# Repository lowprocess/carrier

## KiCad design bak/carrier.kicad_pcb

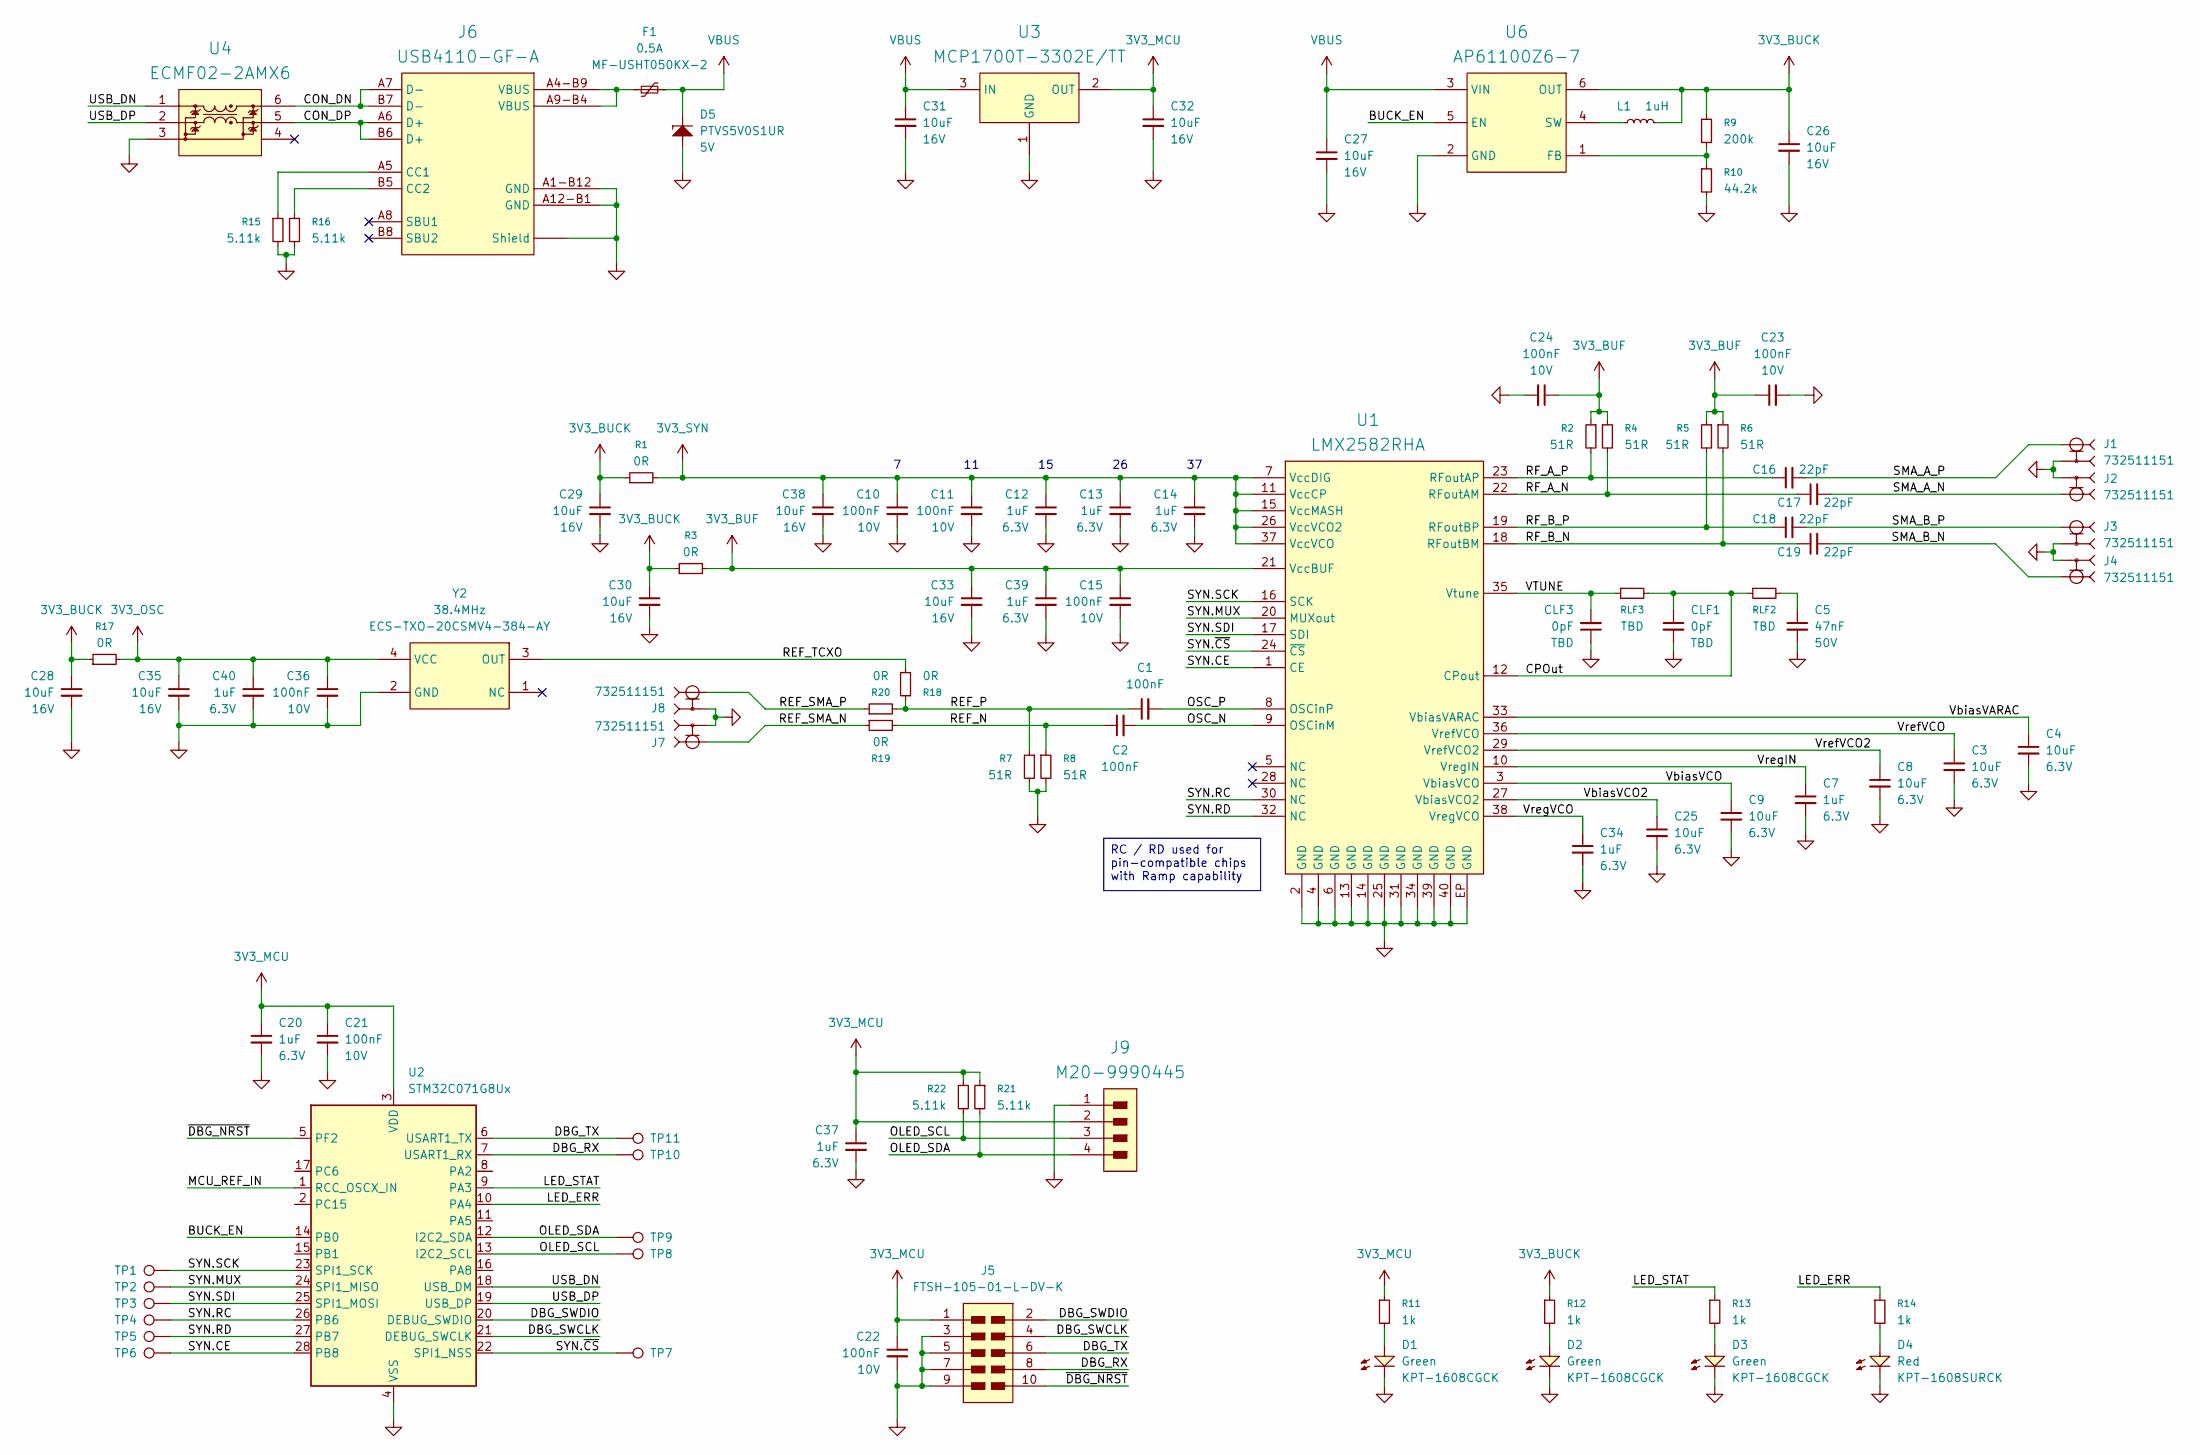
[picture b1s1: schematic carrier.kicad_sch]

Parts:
C1, C2, C10, C11, C15, C21, C22, C23, C24, C36: 100nF; C_0402; Tolerance 10%; Voltage 10V; PartNumber GRM155R71A104K
C3, C4, C8, C9, C25: 10uF; C_0402; Tolerance 20%; Voltage 6.3V; PartNumber GRM155R60J106M
C5: 47nF; C_1206; Tolerance 5%; Voltage 50V; PartNumber C1206C473J5GACTU
C7, C12, C13, C14, C20, C34, C37, C39, C40: 1uF; C_0402; Tolerance 10%; Voltage 6.3V; PartNumber GRM155R70J105K
C16, C17, C18, C19: 22pF; C_0201; Tolerance 5%; Voltage 25V; PartNumber GRM0335C1E220J
C26, C27, C28, C29, C30, C31, C32, C33, C35, C38: 10uF; C_0805; Tolerance 10%; Voltage 16V; PartNumber GRM21BR61C106K
CLF1, CLF3: 0pF; C_0402; Tolerance TBD; Voltage TBD; PartNumber 0402_TBD
D1, D2, D3: Green; LED_0603; PartNumber KPT-1608CGCK
D4: Red; LED_0603; PartNumber KPT-1608SURCK
D5: SOD123W; PartNumber PTVS5V0S1UR
F1: 0.5A; F_1210; PartNumber MF-USHT050KX-2
J1, J2, J3, J4, J7, J8: 732511151; Molex 73251-1151; PartNumber 732511151
J5: FTSH-105-01-L-DV-K; FTSH-105-01-X-DV-K; PartNumber FTSH-105-01-L-DV-K
J6: USB4110-GF-A; USB-C USB4110; PartNumber USB4110-GF-A
J9: M20-9990445; Header 2.54 1x04 Staggered; PartNumber M20-9990445
L1: 1uH; L_252010; Tolerance 20%; PartNumber CIGT252010EH1R0MNE
R1, R3, R17, R18, R19, R20: 0R; R_0402; Tolerance 0%; PartNumber CRCW04020000Z0ED
R2, R4, R5, R6, R7, R8: 51R; R_0201; Tolerance 1%; PartNumber CRCW020151R0FNED
R9: 200k; R_0402; Tolerance 1%; PartNumber RC0402FR-07200KL
R10: 44.2k; R_0402; Tolerance 1%; PartNumber RC0402FR-0744K2L
R11, R12, R13, R14: 1k; R_0402; Tolerance 1%; PartNumber CRCW04021K00FKED
R15, R16, R21, R22: 5.11k; R_0402; Tolerance 1%; PartNumber RC0402FR-075K11L
RLF2, RLF3: TBD; R_0402; Tolerance TBD; PartNumber 0402_TBD
TP1: SCK; Testpad_1mm
TP2: MUX; Testpad_1mm
TP3: SDI; Testpad_1mm
TP4: RC; Testpad_1mm
TP5: RD; Testpad_1mm
TP6: CE; Testpad_1mm
TP7: CS; Testpad_1mm
TP8: SCL; Testpad_1mm
TP9, TP10, TP11: SDA; Testpad_1mm
U1: QFN40; PartNumber LMX2582RHA
U2: STM32C071G8Ux; QFN-28_4x4mm_P0.5mm
U3: SOT-23-3; PartNumber MCP1700T-3302E/TT
U4: DFN6-1.55x1.75; PartNumber ECMF02-2AMX6
U6: SOT563; PartNumber AP61100Z6-7
Y2: 38.4MHz; XTAL2016-4; PartNumber ECS-TXO-20CSMV4-384-AY

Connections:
3V3_BUCK: C26.1, C28.1, C29.1, C30.1, L1.2, R1.1, R3.1, R9.1, R12.1, R17.1, U6.6 (OUT)
3V3_BUF: C15.1, C23.1, C24.1, C33.1, C39.1, R2.1, R3.2, R4.1, R5.1, R6.1, U1.21 (VccBUF)
3V3_MCU: C20.1, C21.1, C22.1, C32.1, C37.1, J5.1, J9.2, R11.1, R21.1, R22.1, U2.3 (VDD), U3.2 (OUT)
3V3_OSC: C35.1, C36.1, C40.1, R17.2, Y2.4 (VCC)
3V3_SYN: C10.1, C11.1, C12.1, C13.1, C14.1, C38.1, R1.2, U1.7 (VccDIG), U1.11 (VccCP), U1.15 (VccMASH), U1.26 (VccVCO2), U1.37 (VccVCO)
/BUCK_EN: U2.14 (PB0), U6.5 (EN)
/CON_DN: J6.A7 (D-), J6.B7 (D-), U4.6 (IC+)
/CON_DP: J6.A6 (D+), J6.B6 (D+), U4.5 (IC-)
/CPOut: CLF1.1, RLF2.1, RLF3.2, U1.12 (CPout)
/DBG_RX: J5.8, TP10.1 (1_1), U2.7 (USART1_RX)
/DBG_SWCLK: J5.4, U2.21 (DEBUG_SWCLK)
/DBG_SWDIO: J5.2, U2.20 (DEBUG_SWDIO)
/DBG_TX: J5.6, TP11.1 (1_1), U2.6 (USART1_TX)
/LED_ERR: R14.1, U2.10 (PA4)
/LED_STAT: R13.1, U2.9 (PA3)
/MCU_REF_IN: U2.1 (RCC_OSCX_IN)
/OLED_SCL: J9.3, R22.2, TP8.1 (1_1), U2.13 (I2C2_SCL)
/OLED_SDA: J9.4, R21.2, TP9.1 (1_1), U2.12 (I2C2_SDA)
/OSC_N: C2.2, U1.9 (OSCinM)
/OSC_P: C1.2, U1.8 (OSCinP)
/REF_N: C2.1, R8.1, R19.2
/REF_P: C1.1, R7.1, R18.2, R20.2
/REF_SMA_N: J7.inner (Inner), R19.1
/REF_SMA_P: J8.inner (Inner), R20.1
/REF_TCXO: R18.1, Y2.3 (OUT)
/RF_A_N: C17.1, R4.2, U1.22 (RFoutAM)
/RF_A_P: C16.1, R2.2, U1.23 (RFoutAP)
/RF_B_N: C19.1, R6.2, U1.18 (RFoutBM)
/RF_B_P: C18.1, R5.2, U1.19 (RFoutBP)
/SMA_A_N: C17.2, J2.inner (Inner)
/SMA_A_P: C16.2, J1.inner (Inner)
/SMA_B_N: C19.2, J4.inner (Inner)
/SMA_B_P: C18.2, J3.inner (Inner)
/SYN.CE: TP6.1 (1_1), U1.1 (CE), U2.28 (PB8)
/SYN.MUX: TP2.1 (1_1), U1.20 (MUXout), U2.24 (SPI1_MISO)
/SYN.RC: TP4.1 (1_1), U1.30 (NC), U2.26 (PB6)
/SYN.RD: TP5.1 (1_1), U1.32 (NC), U2.27 (PB7)
/SYN.SCK: TP1.1 (1_1), U1.16 (SCK), U2.23 (SPI1_SCK)
/SYN.SDI: TP3.1 (1_1), U1.17 (SDI), U2.25 (SPI1_MOSI)
/SYN.~CS: TP7.1 (1_1), U1.24 (~CS), U2.22 (SPI1_NSS)
/USB_DN: U2.18 (USB_DM), U4.1 (CON+)
/USB_DP: U2.19 (USB_DP), U4.2 (CON-)
/VTUNE: CLF3.2, RLF3.1, U1.35 (Vtune)
/VbiasVARAC: C4.1, U1.33 (VbiasVARAC)
/VbiasVCO: C9.1, U1.3 (VbiasVCO)
/VbiasVCO2: C25.1, U1.27 (VbiasVCO2)
/VrefVCO: C3.1, U1.36 (VrefVCO)
/VrefVCO2: C8.1, U1.29 (VrefVCO2)
/VregIN: C7.1, U1.10 (VregIN)
/VregVCO: C34.1, U1.38 (VregVCO)
/~DBG_NRST: J5.10, U2.5 (PF2)
GND: C3.2, C4.2, C5.2, C7.2, C8.2, C9.2, C10.2, C11.2, C12.2, C13.2, C14.2, C15.2, C20.2, C21.2, C22.2, C23.2, C24.2, C25.2, C26.2, C27.2, C28.2, C29.2, C30.2, C31.2, C32.2, C33.2, C34.2, C35.2, C36.2, C37.2, C38.2, C39.2, C40.2, CLF1.2, CLF3.1, D1.K, D2.K, D3.K, D4.K, D5.A, J1.outer (Outer), J2.outer (Outer), J3.outer (Outer), J4.outer (Outer), J5.3, J5.5, J5.7, J5.9, J6.A1-B12 (GND), J6.A12-B1 (GND), J6.SH (Shield), J7.outer (Outer), J8.outer (Outer), J9.1, R7.2, R8.2, R10.2, R15.2, R16.2, U1.2 (GND), U1.4 (GND), U1.6 (GND), U1.13 (GND), U1.14 (GND), U1.25 (GND), U1.31 (GND), U1.34 (GND), U1.39 (GND), U1.40 (GND), U1.EP (GND), U2.4 (VSS), U3.1 (GND), U4.3 (GND), U6.2 (GND), Y2.2 (GND); also elsewhere on the board
unnamed 52: C5.1, RLF2.2; also elsewhere on the board
unnamed: D1.A, R11.2
unnamed: D2.A, R12.2
unnamed: D3.A, R13.2
unnamed: D4.A, R14.2
unnamed: F1.1, J6.A4-B9 (VBUS), J6.A9-B4 (VBUS)
unnamed: J6.A5 (CC1), R15.1
unnamed: J6.B5 (CC2), R16.1
unnamed: R9.2, R10.1, U6.1 (FB)
unnamed: L1.1, U6.4 (SW)
VBUS: C27.1, C31.1, D5.K, F1.2, U3.3 (IN), U6.3 (VIN)

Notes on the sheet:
RC / RD used for pin-compatible chips with Ramp capability

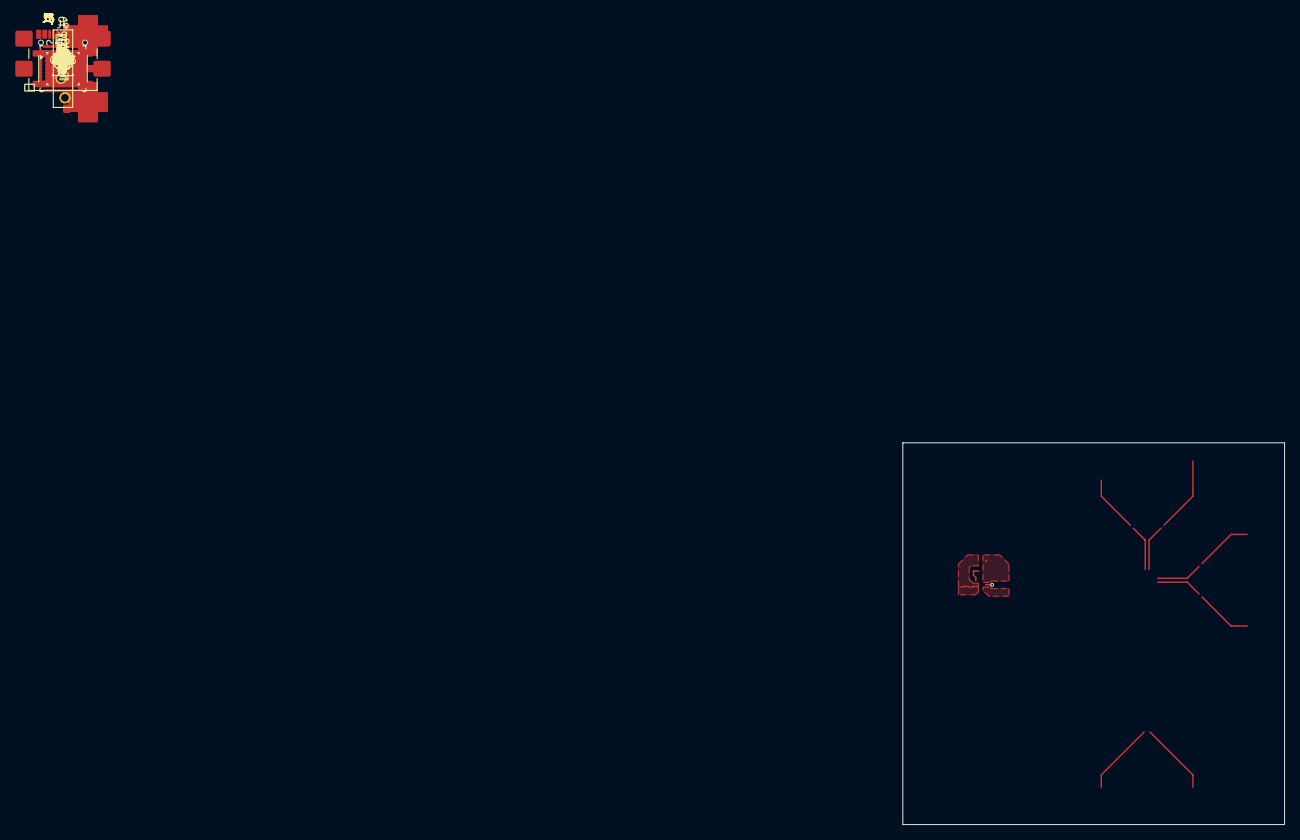
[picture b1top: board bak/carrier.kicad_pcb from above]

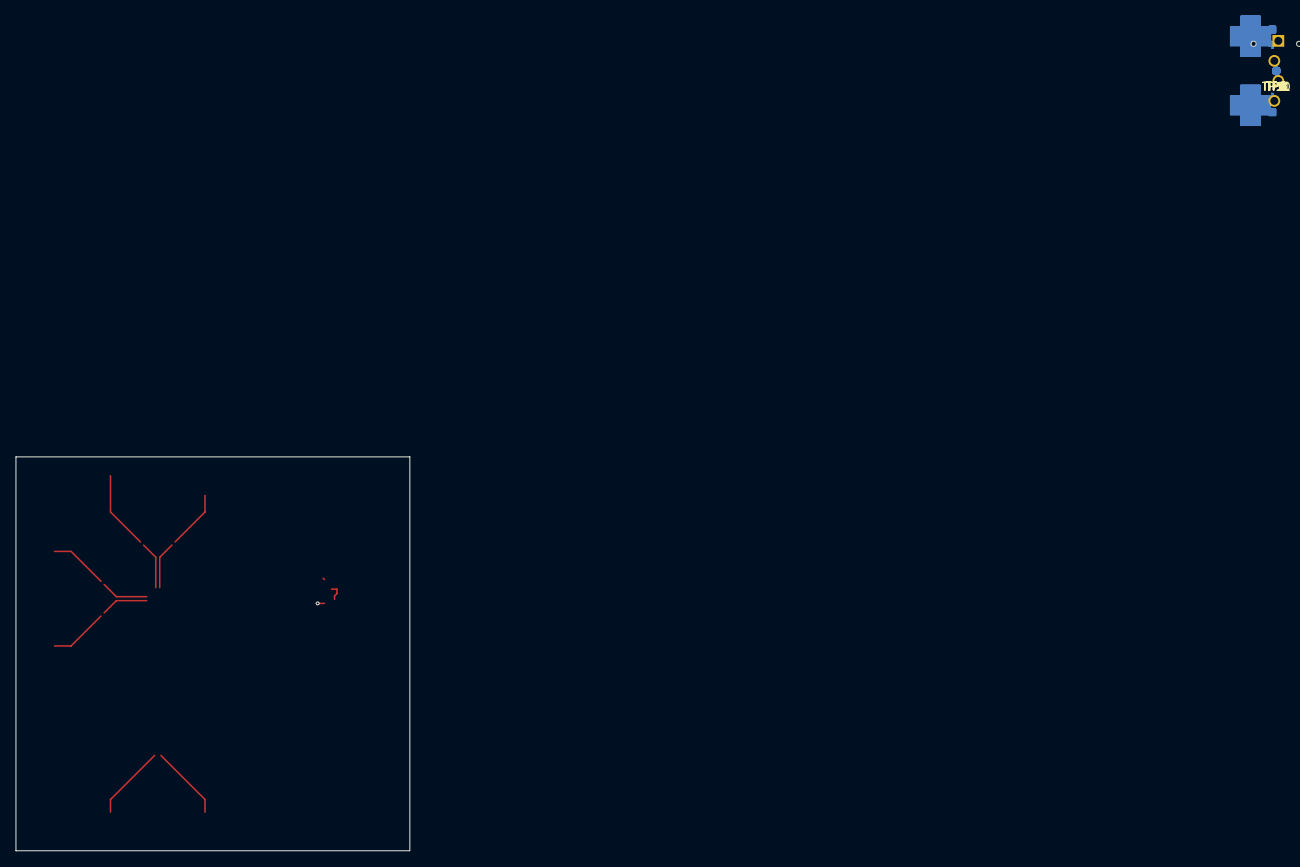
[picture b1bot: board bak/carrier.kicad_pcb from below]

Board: 2 copper layers, 50.0 x 50.0 mm, 98 parts (11 on the bottom side), 62 nets.

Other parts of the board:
CLF2: 0pF; C_0402

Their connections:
GND: CLF2.2; also elsewhere on the board
unnamed 52: CLF2.1; also elsewhere on the board

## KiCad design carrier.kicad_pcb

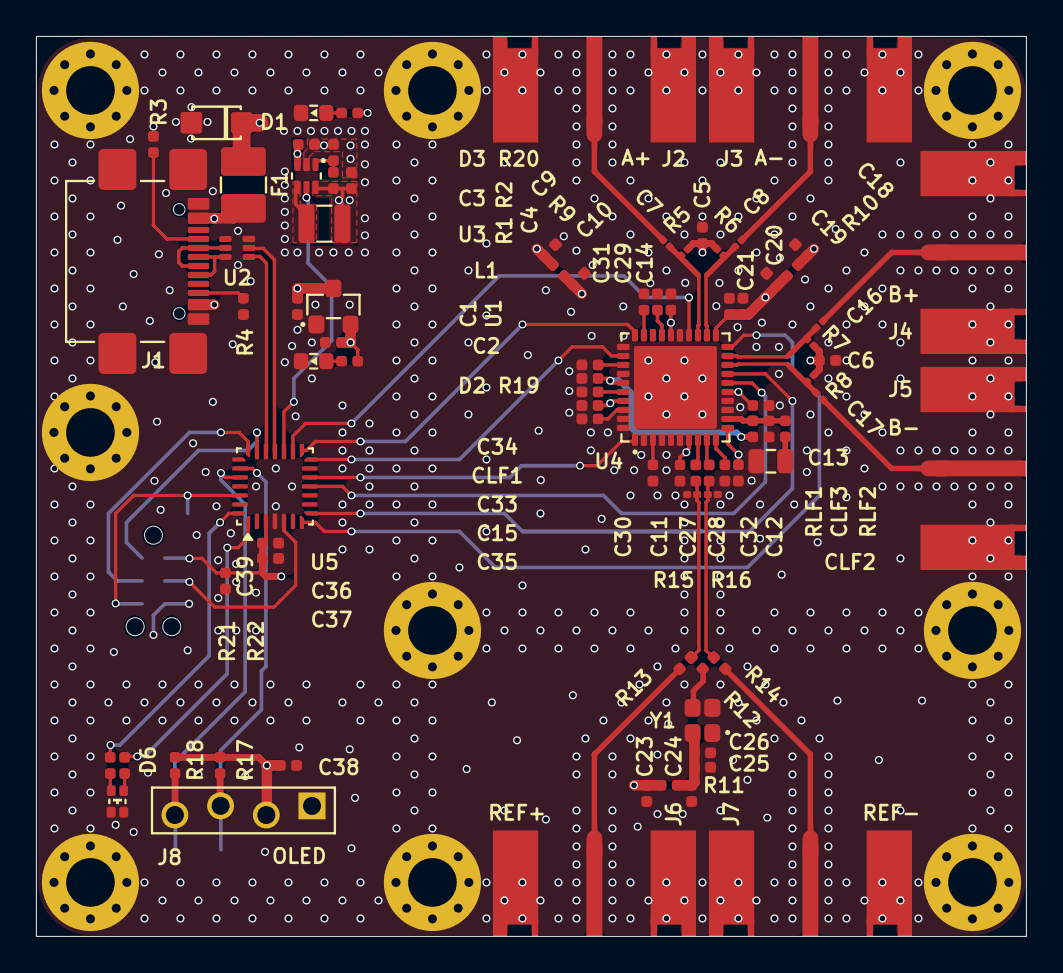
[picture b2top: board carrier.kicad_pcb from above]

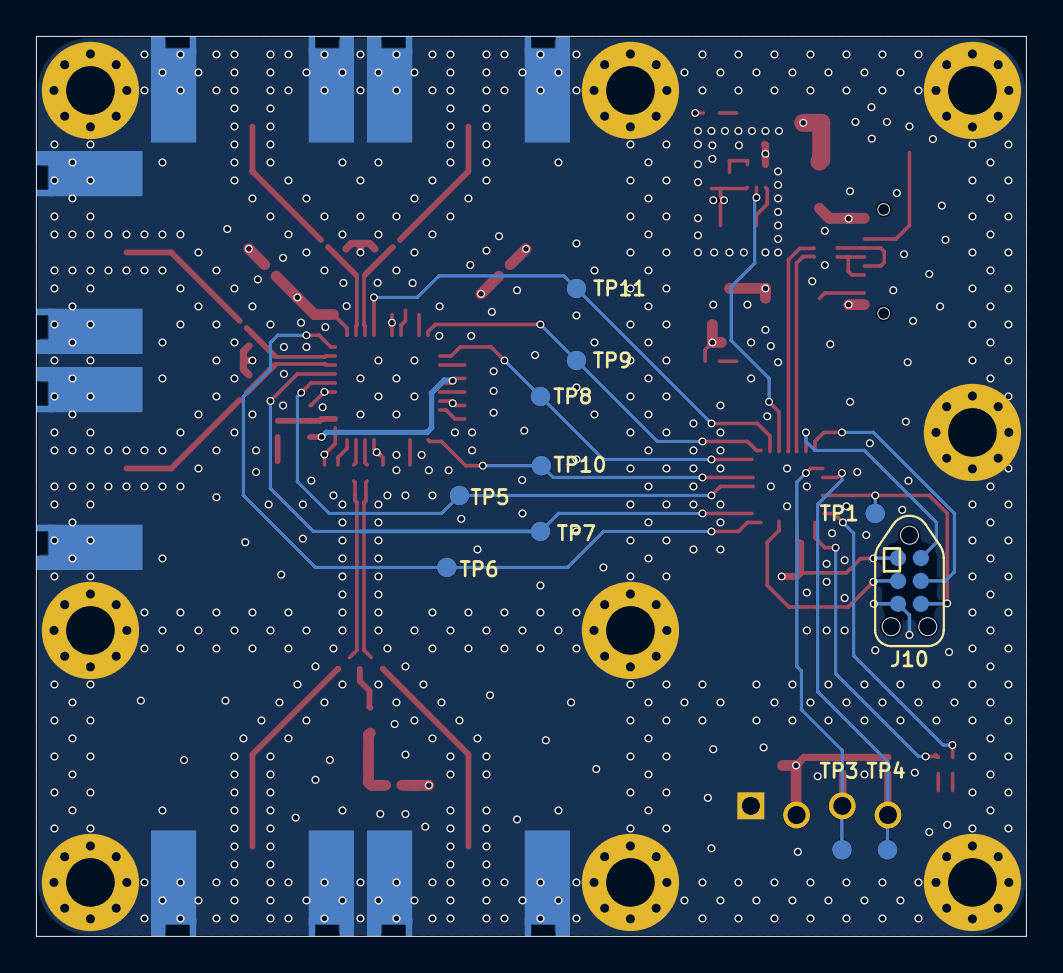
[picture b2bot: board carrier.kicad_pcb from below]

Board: 4 copper layers, 55.0 x 50.0 mm, 105 parts (11 on the bottom side), 61 nets.

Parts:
C1, C2, C3, C4, C9, C10, C18, C19, C23, C24, C29, C30, C31, C33, C34: 10uF; C_0402
C5, C6, C11, C12, C21, C26, C27, C28, C37, C39: 100nF; C_0402
C7, C8, C16, C17: 22pF; C_0201
C13, C14, C15, C20, C25, C32, C35, C36, C38: 1uF; C_0402
CLF1, CLF3: 0pF; C_0402
CLF2: 10nF; C_0805
D1: SOD123W
D2, D3: Green; LED_0603
D6: RG; APHB1608GR
F1: 0.5A; F_1210
H1, H2, H3, H4, H5, H6, H7, H8, H9: GND; MountingHole_2.7mm_M2.5_Pad_Via
J1: USB4110-GF-A; USB-C USB4110
J2, J3, J4, J5, J6, J7: 732511151; Molex 73251-1151
J8: M20-9990445; Header 2.54 1x04 Staggered
J10: TC2030-NL-FP; TC2030-xxx-NL
L1: 1uH; L_252010
R1: 200k; R_0402
R2: 44.2k; R_0402
R3, R4, R17, R18: 5.11k; R_0402
R5, R6, R7, R8, R15, R16: 51R; R_0201
R9, R10, R11, R12, R13, R14: 0R; R_0402
R19, R20, R21, R22: 1k; R_0402
RLF1, RLF2: TBD; R_0402
TP1, TP3: SDA; Testpad_1mm
TP4: SCL; Testpad_1mm
TP5: SCK; Testpad_1mm
TP6: MUX; Testpad_1mm
TP7: SDI; Testpad_1mm
TP8: RC; Testpad_1mm
TP9: RD; Testpad_1mm
TP10: CE; Testpad_1mm
TP11: CS; Testpad_1mm
U1: SOT-23-3
U2: DFN6-1.55x1.75
U3: SOT563
U4: QFN40
U5: STM32C071G8Ux; QFN-28_4x4mm_P0.5mm
Y1: 38.4MHz; XTAL2016-4

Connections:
3V3_BUCK: C4.1, C9.1, C18.1, L1.2, R1.1, R9.1, R10.1, R20.1, U3.6 (OUT)
3V3_BUF: C5.1, C6.1, C19.1, C20.1, C21.1, R5.1, R6.1, R7.1, R8.1, R10.2, U4.21 (VccBUF)
3V3_MCU: C2.1, C23.1, C36.1, C37.1, C38.1, C39.1, J8.2, J10.1, R11.1, R17.1, R18.1, R19.1, U1.2 (OUT), U5.3 (VDD)
3V3_OSC: C24.1, C25.1, C26.1, R11.2, Y1.4 (VCC)
3V3_SYN: C10.1, C11.1, C12.1, C13.1, C14.1, C15.1, R9.2, U4.7 (VccDIG), U4.11 (VccCP), U4.15 (VccMASH), U4.26 (VccVCO2), U4.37 (VccVCO)
/BUCK_EN: U3.5 (EN), U5.17 (PC6)
/CON_DN: J1.A7 (D-), J1.B7 (D-), U2.5 (IC-)
/CON_DP: J1.A6 (D+), J1.B6 (D+), U2.6 (IC+)
/CPOut: CLF3.1, RLF1.2, RLF2.1, U4.12 (CPout)
/DBG_SWCLK: J10.4, U5.21 (DEBUG_SWCLK)
/DBG_SWDIO: J10.2, U5.20 (DEBUG_SWDIO)
/DBG_TX: J10.6, TP1.1 (1_1), U5.26 (USART1_TX)
/LED_ERR: R22.1, U5.1 (PC14)
/LED_STAT: R21.1, U5.28 (PB8)
/OLED_SCL: J8.3, R17.2, TP3.1 (1_1), U5.23 (I2C2_SCL)
/OLED_SDA: J8.4, R18.2, TP4.1 (1_1), U5.24 (I2C2_SDA)
/OSC_N: C28.2, U4.9 (OSCinM)
/OSC_P: C27.2, U4.8 (OSCinP)
/REF_N: C28.1, R14.2, R16.1
/REF_P: C27.1, R12.2, R13.2, R15.1
/REF_SMA_N: J7.inner (Inner), R14.1
/REF_SMA_P: J6.inner (Inner), R13.1
/REF_TCXO: R12.1, Y1.3 (OUT)
/RF_A_N: C8.1, R6.2, U4.22 (RFoutAM)
/RF_A_P: C7.1, R5.2, U4.23 (RFoutAP)
/RF_B_N: C17.1, R8.2, U4.18 (RFoutBM)
/RF_B_P: C16.1, R7.2, U4.19 (RFoutBP)
/SMA_A_N: C8.2, J3.inner (Inner)
/SMA_A_P: C7.2, J2.inner (Inner)
/SMA_B_N: C17.2, J5.inner (Inner)
/SMA_B_P: C16.2, J4.inner (Inner)
/SYN.CE: TP10.1 (1_1), U4.1 (CE), U5.12 (PA6)
/SYN.MUX: TP6.1 (1_1), U4.20 (MUXout), U5.7 (PA1)
/SYN.RC: TP9.1 (1_1), U4.30 (NC), U5.15 (PB1)
/SYN.RD: TP8.1 (1_1), U4.32 (NC), U5.14 (PB0)
/SYN.SCK: TP5.1 (1_1), U4.16 (SCK), U5.11 (SPI1_SCK)
/SYN.SDI: TP7.1 (1_1), U4.17 (SDI), U5.8 (SPI1_MOSI)
/SYN.~CS: TP11.1 (1_1), U4.24 (~CS), U5.16 (PA8)
/USB_DN: U2.2 (CON-), U5.18 (USB_DM)
/USB_DP: U2.1 (CON+), U5.19 (USB_DP)
/VTUNE: CLF1.2, RLF1.1, U4.35 (Vtune)
/VbiasVARAC: C34.1, U4.33 (VbiasVARAC)
/VbiasVCO: C30.1, U4.3 (VbiasVCO)
/VbiasVCO2: C29.1, U4.27 (VbiasVCO2)
/VrefVCO: C33.1, U4.36 (VrefVCO)
/VrefVCO2: C31.1, U4.29 (VrefVCO2)
/VregIN: C32.1, U4.10 (VregIN)
/VregVCO: C35.1, U4.38 (VregVCO)
/~DBG_NRST: J10.3, U5.5 (PF2)
GND: C1.2, C2.2, C3.2, C4.2, C5.2, C6.2, C9.2, C10.2, C11.2, C12.2, C13.2, C14.2, C15.2, C18.2, C19.2, C20.2, C21.2, C23.2, C24.2, C25.2, C26.2, C29.2, C30.2, C31.2, C32.2, C33.2, C34.2, C35.2, C36.2, C37.2, C38.2, C39.2, CLF1.1, CLF2.2, CLF3.2, D1.A, D2.K, D3.K, D6.GK (Green_K), D6.RK (Red_K), H1.1 (1_1), H2.1 (1_1), H3.1 (1_1), H4.1 (1_1), H5.1 (1_1), H6.1 (1_1), H7.1 (1_1), H8.1 (1_1), H9.1 (1_1), J1.A1-B12 (GND), J1.A12-B1 (GND), J1.SH (Shield), J2.outer (Outer), J3.outer (Outer), J4.outer (Outer), J5.outer (Outer), J6.outer (Outer), J7.outer (Outer), J8.1, J10.5, R2.2, R3.2, R4.2, R15.2, R16.2, U1.1 (GND), U2.3 (GND), U3.2 (GND), U4.2 (GND), U4.4 (GND), U4.6 (GND), U4.13 (GND), U4.14 (GND), U4.25 (GND), U4.31 (GND), U4.34 (GND), U4.39 (GND), U4.40 (GND), U4.EP (GND), U5.4 (VSS), Y1.2 (GND)
unnamed: CLF2.1, RLF2.2
unnamed: D2.A, R19.2
unnamed: D3.A, R20.2
unnamed: D6.RA (Red_A), R21.2
unnamed: D6.GA (Green_A), R22.2
unnamed: F1.1, J1.A4-B9 (VBUS), J1.A9-B4 (VBUS)
unnamed: J1.A5 (CC1), R3.1
unnamed: J1.B5 (CC2), R4.1
unnamed: R1.2, R2.1, U3.1 (FB)
unnamed: L1.1, U3.4 (SW)
VBUS: C1.1, C3.1, D1.K, F1.2, U1.3 (IN), U3.3 (VIN)
